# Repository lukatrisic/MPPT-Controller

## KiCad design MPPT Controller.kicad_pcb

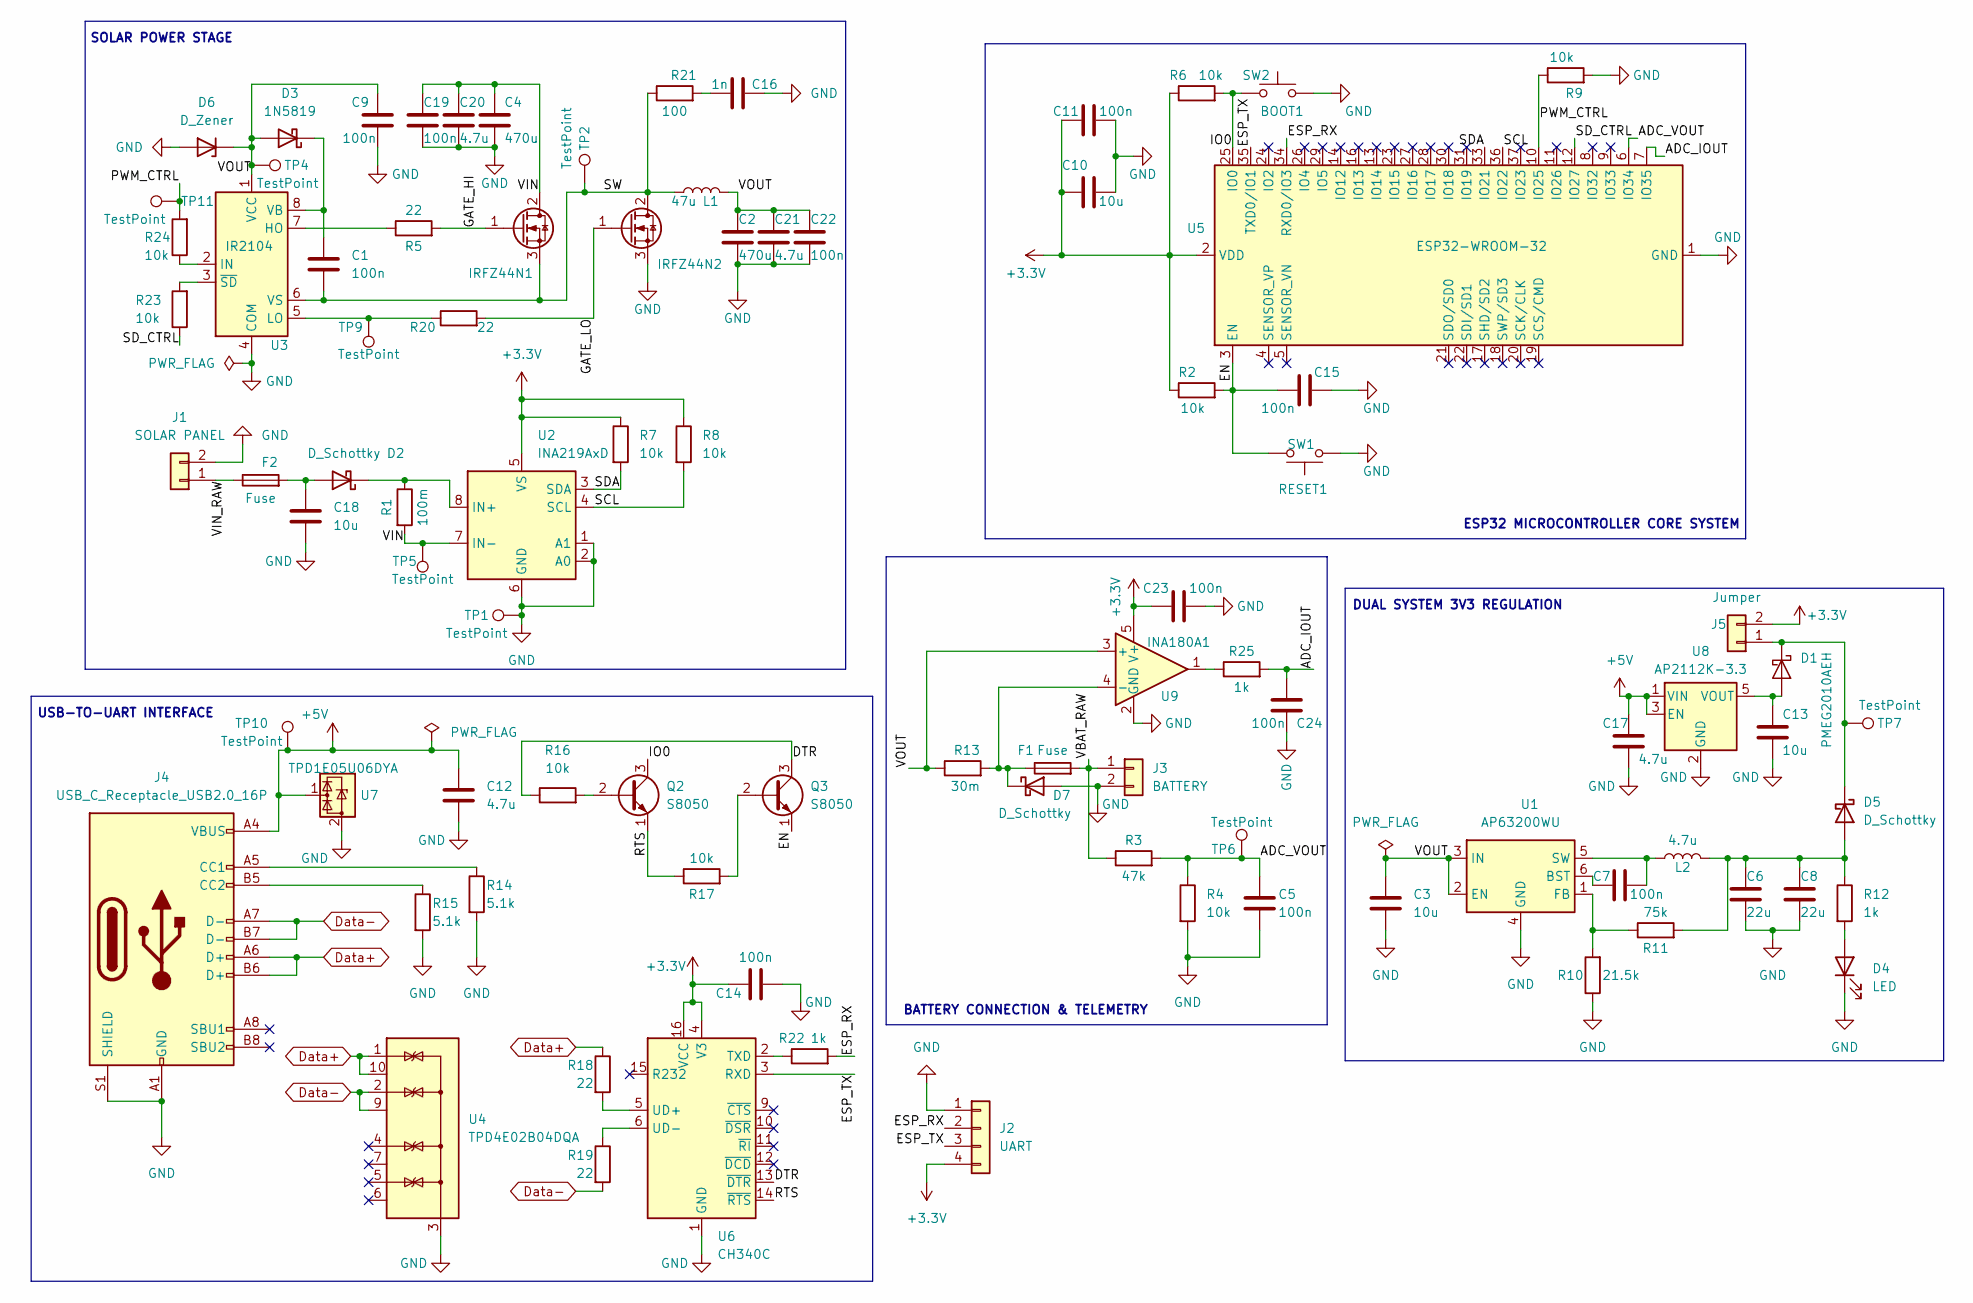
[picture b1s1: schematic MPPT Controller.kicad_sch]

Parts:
C1, C5, C7, C9, C11, C14, C15, C19, C22: 100n; C_0805_2012Metric
C2, C4: 470u; CP_Radial_D10.0mm_P5.00mm
C3, C10, C13, C18: 10u; C_0805_2012Metric
C6, C8: 22u; C_0805_2012Metric
C12, C17, C20, C21: 4.7u; C_0805_2012Metric
C16: 1n; C_0805_2012Metric
C23, C24: 100n; C_0603_1608Metric_Pad1.08x0.95mm_HandSolder
D1: PMEG2010AEH; D_SOD-123F
D2: D_Schottky; D_DO-201AD_P15.24mm_Horizontal
D3: 1N5819; D_DO-41_SOD81_P10.16mm_Horizontal
D4: LED; LED_0603_1608Metric
D5: D_Schottky; D_SOD-123
D6: D_Zener; D_SOD-123
D7: D_Schottky; ST_D_SMC
F1, F2: Fuse; Fuseholder_Cylinder-5x20mm_Schurter_0031_8201_Horizontal_Op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
IRFZ44N1, IRFZ44N2: Q_NMOS_GDS; TO-220-3_Vertical
J1: SOLAR PANEL; TerminalBlock_Phoenix_MKDS-1,5-2-5.08_1x02_P5.08mm_Horizont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
J2: UART; PinHeader_1x04_P2.54mm_Vertical
J3: BATTERY; TerminalBlock_Phoenix_MKDS-1,5-2-5.08_1x02_P5.08mm_Horizont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
J4: USB_C_Receptacle_USB2.0_16P; USB_C_Receptacle_HRO_TYPE-C-31-M-12
J5: Jumper; PinHeader_1x02_P2.54mm_Vertical
L1: 47u; L_Bourns_SRR1260
L2: 4.7u; L_Taiyo-Yuden_NR-40xx
Q2, Q3: S8050; SOT-23
R1: 100m; R_2512_6332Metric
R2, R4, R6, R7, R8, R9, R16, R17, R23, R24: 10k; R_0805_2012Metric
R3: 47k; R_0805_2012Metric
R5, R20: 22; R_0805_2012Metric
R10: 21.5k; R_0805_2012Metric
R11: 75k; R_0805_2012Metric
R12, R22: 1k; R_0805_2012Metric
R13: 30m; R_2010_5025Metric
R14, R15: 5.1k; R_0805_2012Metric
R18, R19: 22; R_0402_1005Metric
R21: 100; R_0805_2012Metric
R25: 1k; R_0603_1608Metric_Pad0.98x0.95mm_HandSolder
SW1: RESET1; SW_SPST_B3U-1000P
SW2: BOOT1; SW_SPST_B3U-1000P
TP1, TP2, TP4, TP5, TP6, TP7, TP9, TP10, TP11: TestPoint; TestPoint_Pad_D1.5mm
U1: AP63200WU; TSOT-23-6
U2: INA219AxD; SOIC-8_3.9x4.9mm_P1.27mm
U3: IR2104; SOIC-8_3.9x4.9mm_P1.27mm
U4: TPD4E02B04DQA; USON-10_2.5x1.0mm_P0.5mm
U5: ESP32-WROOM-32
U6: CH340C; SOIC-16_3.9x9.9mm_P1.27mm
U7: TPD1E05U06DYA; D_SOD-523
U8: AP2112K-3.3; SOT-23-5
U9: INA180A1; SOT-23-5

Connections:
+3.3V: C10.1, C11.1, C14.1, C23.1, J2.4, J5.2, R2.1, R6.1, R7.1, R8.1, U2.5 (VS), U5.2 (VDD), U6.4 (V3), U6.16 (VCC), U9.5 (V+)
+5V: C12.1, C17.1, J4.A4 (VBUS), J4.A9 (VBUS), J4.B4 (VBUS), J4.B9 (VBUS), TP10.1, U7.1 (I/O), U8.1 (VIN), U8.3 (EN)
/ADC_IOUT: C24.1, R25.2, U5.7 (IO35)
/ADC_VOUT: C5.1, R3.2, R4.1, TP6.1, U5.6 (IO34)
/DTR: Q3.3 (C), R16.1, U6.13 (~DTR)
/EN: C15.1, Q3.1 (E), R2.2, SW1.2, U5.3 (EN); also elsewhere on the board
/ESP_RX: J2.2, R22.2, U5.34 (RXD0/IO3)
/ESP_TX: J2.3, U5.35 (TXD0/IO1), U6.3 (RXD)
/GATE_HI: IRFZ44N1.1 (G), R5.2
/GATE_LO: IRFZ44N2.1 (G), R20.2
/IO0: Q2.3 (C), R6.2, SW2.1, U5.25 (IO0); also elsewhere on the board
/PWM_CTRL: R9.1, R24.2, TP11.1, U5.10 (IO25)
/RTS: Q2.1 (E), R17.1, U6.14 (~RTS)
/SCL: R8.2, U2.4 (SCL), U5.36 (IO22)
/SDA: R7.2, U2.3 (SDA), U5.33 (IO21)
/SD_CTRL: R23.1, U5.12 (IO27)
/SW: C1.2, IRFZ44N1.3 (S), IRFZ44N2.2 (D), L1.1, R21.1, TP2.1, U3.6 (VS)
/VBAT_RAW: F1.2, J3.1, R3.1
/VIN: C4.1, C19.1, C20.1, IRFZ44N1.2 (D), R1.2, TP5.1, U2.7 (IN-)
/VIN_RAW: F2.1, J1.1
/VOUT: C2.1, C3.1, C9.1, C21.1, C22.1, D3.2 (A), D6.1 (K), L1.2, R13.1, TP4.1, U1.2 (EN), U1.3 (IN), U3.1 (VCC), U9.3 (+)
Data+: J4.A6 (D+), J4.B6 (D+), R18.1, U4.1 (IO1), U4.10 (NC)
Data-: J4.A7 (D-), J4.B7 (D-), R19.2, U4.2 (IO2), U4.9 (NC)
GND: C2.2, C3.2, C4.2, C5.2, C6.2, C8.2, C9.2, C10.2, C11.2, C12.2, C13.2, C14.2, C15.2, C16.2, C17.2, C18.2, C19.2, C20.2, C21.2, C22.2, C23.2, C24.2, D4.1 (K), D6.2 (A), D7.2 (A), IRFZ44N2.3 (S), J1.2, J2.1, J3.2, J4.A1 (GND), J4.A12 (GND), J4.B1 (GND), J4.B12 (GND), J4.S1 (SHIELD), R4.2, R9.2, R10.1, R14.2, R15.2, SW1.1, SW2.2, TP1.1, U1.4 (GND), U2.1 (A1), U2.2 (A0), U2.6 (GND), U3.4 (COM), U4.3 (G), U4.8 (G), U5.1 (GND), U5.15 (GND), U5.38 (GND), U5.39 (GND), U6.1 (GND), U7.2 (GND), U8.2 (GND), U9.2 (GND); also elsewhere on the board
unnamed: C16.1, R21.2
unnamed: C13.1, D1.2 (A), U8.5 (VOUT)
unnamed: D1.1 (K), D5.1 (K), J5.1, TP7.1
unnamed: C18.1, D2.2 (A), F2.2
unnamed: D2.1 (K), R1.1, U2.8 (IN+)
unnamed: C1.1, D3.1 (K), U3.8 (VB)
unnamed: D4.2 (A), R12.2
unnamed: C6.1, C8.1, D5.2 (A), L2.2, R11.2, R12.1
unnamed: D7.1 (K), F1.1, R13.2, U9.4 (-)
unnamed: J4.A5 (CC1), R14.1
unnamed: J4.B5 (CC2), R15.1
unnamed: Q2.2 (B), R16.2
unnamed: Q3.2 (B), R17.2
unnamed: R25.1, U9.1
unnamed: C7.1, U1.6 (BST)
unnamed: R10.2, R11.1, U1.1 (FB)
unnamed: C7.2, L2.1, U1.5 (SW)
unnamed: R5.1, U3.7 (HO)
unnamed: R24.1, U3.2 (IN)
unnamed: R20.1, TP9.1, U3.5 (LO)
unnamed: R23.2, U3.3 (~SD)
unnamed: R22.1, U6.2 (TXD)
unnamed: R18.2, U6.5 (UD+)
unnamed: R19.1, U6.6 (UD-)

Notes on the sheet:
DUAL SYSTEM 3V3 REGULATION
SOLAR POWER STAGE
BATTERY CONNECTION & TELEMETRY
USB-TO-UART INTERFACE
ESP32 MICROCONTROLLER CORE SYSTEM

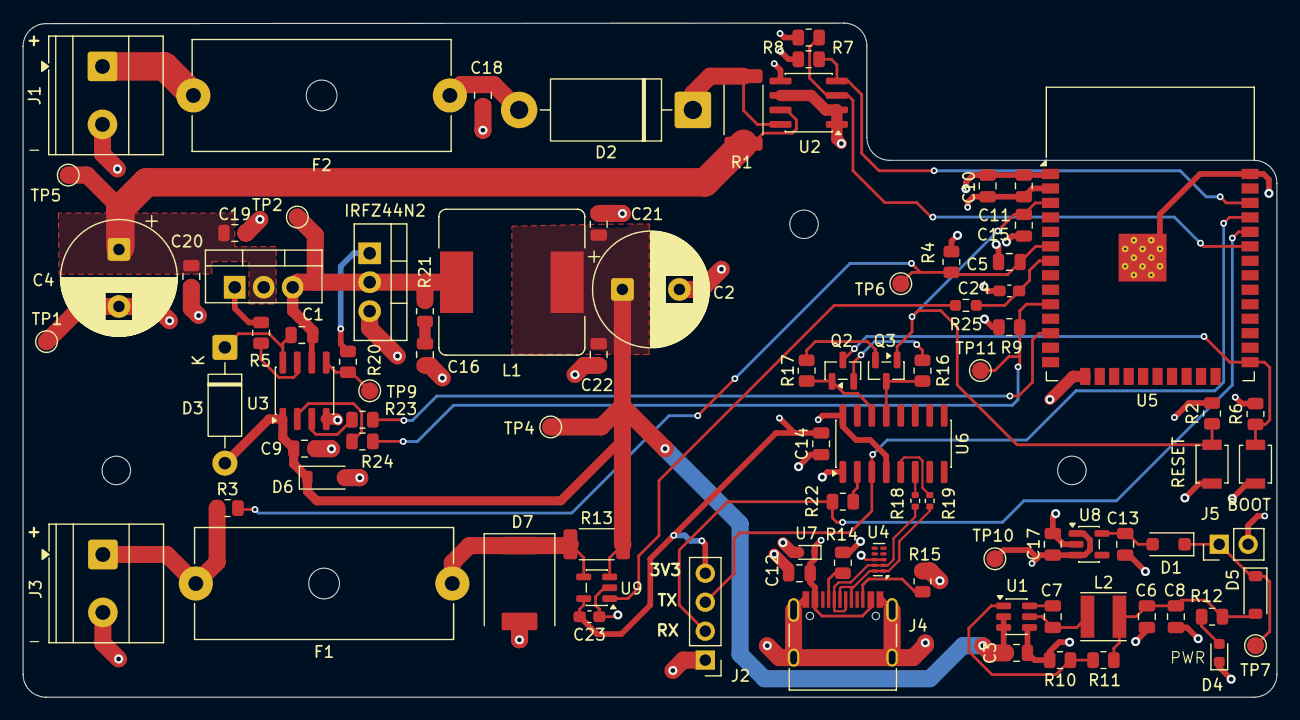
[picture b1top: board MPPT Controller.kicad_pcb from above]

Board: 4 copper layers, 110.0 x 59.1 mm, 89 parts (0 on the bottom side), 48 nets.

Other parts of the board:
BOOT: BOOT1; SW_SPST_B3U-1000P
RESET: RESET1; SW_SPST_B3U-1000P

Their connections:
/EN: RESET.2; also elsewhere on the board
/IO0: BOOT.1; also elsewhere on the board
GND: BOOT.2, RESET.1; also elsewhere on the board
